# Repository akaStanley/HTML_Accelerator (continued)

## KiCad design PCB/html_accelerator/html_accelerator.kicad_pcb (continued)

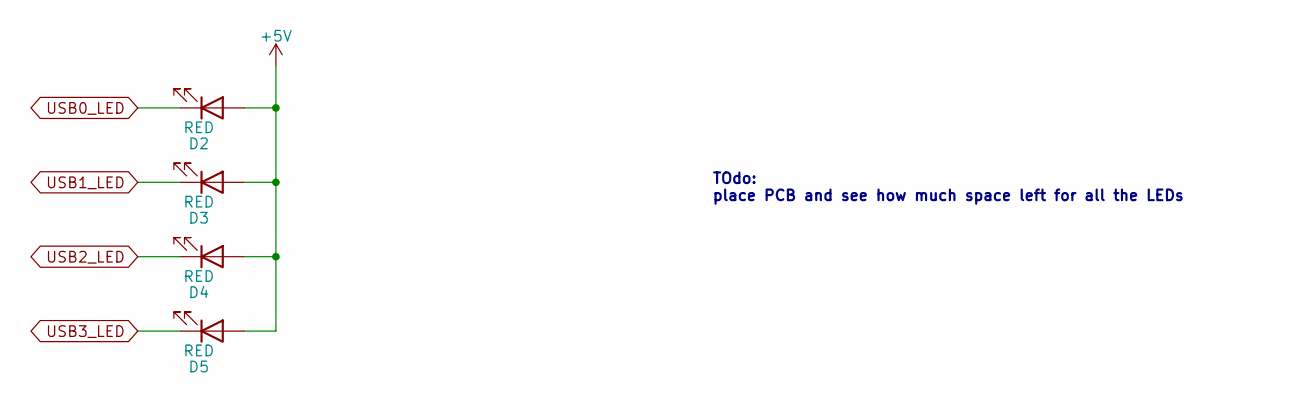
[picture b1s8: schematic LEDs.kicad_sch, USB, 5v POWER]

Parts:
D2, D3, D4, D5: RED; LED_0805_2012Metric_Pad1.15x1.40mm_HandSolder

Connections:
+5V: D2.2 (A), D3.2 (A), D4.2 (A), D5.2 (A); also elsewhere on the board
USB0_LED: D2.1 (K); also elsewhere on the board
USB1_LED: D3.1 (K); also elsewhere on the board
USB2_LED: D4.1 (K); also elsewhere on the board
USB3_LED: D5.1 (K); also elsewhere on the board

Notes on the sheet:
TOdo: place PCB and see how much space left for all the LEDs

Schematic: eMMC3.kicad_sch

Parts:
C52, C53: 4.7uF; C_0805_2012Metric_Pad1.18x1.45mm_HandSolder
C54, C55: 22pF; C_0805_2012Metric_Pad1.18x1.45mm_HandSolder
C56, C57: 2.2uF; C_0805_2012Metric_Pad1.18x1.45mm_HandSolder
C58: 0.1uF; C_0805_2012Metric_Pad1.18x1.45mm_HandSolder
R50: 10k; R_0805_2012Metric_Pad1.20x1.40mm_HandSolder
R51: 1k; R_0805_2012Metric_Pad1.20x1.40mm_HandSolder
R52: 27; R_0805_2012Metric_Pad1.20x1.40mm_HandSolder
R53: 680; R_0805_2012Metric_Pad1.20x1.40mm_HandSolder
U6, U7: EMMC_4G; EMMC04G-M627-X03U_KNT
U9: AU6438BS; SSOP-28_3.9x9.9mm_P0.635mm
Y4: 12MHz; Crystal_SMD_3225-4Pin_3.2x2.5mm

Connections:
90_USB2_D_N: U9.8 (USB_DN); also elsewhere on the board
90_USB2_D_P: U9.7 (USB_DP); also elsewhere on the board
+5V: R50.1, U9.15 (AVDD_5.0_IN); also elsewhere on the board
/eMMC3/DATA_0: U7.A3 (DAT0), U9.27 (DATA0)
/eMMC3/DATA_1: U7.A4 (DAT1), U9.28 (DATA1)
/eMMC3/DATA_2: U7.A5 (DAT2), U9.19 (DATA2)
/eMMC3/DATA_3: U7.B2 (DAT3), U9.20 (DATA3)
/eMMC3/DATA_4: U7.B3 (DAT4), U9.21 (DATA4)
/eMMC3/DATA_5: U7.B4 (DAT5), U9.23 (DATA5)
/eMMC3/DATA_6: U7.B5 (DAT6), U9.25 (DATA6)
/eMMC3/DATA_7: U7.B6 (DAT7), U9.26 (DATA7)
/eMMC3/VDD_3v3_EMMC3: C52.1, C53.1, C56.1, C57.1, U7.C6 (VCCQ), U7.E6 (VCC), U7.F5 (VCC), U7.J10 (VCC), U7.K9 (VCC), U7.M4 (VCCQ), U7.N4 (VCCQ), U7.P3 (VCCQ), U7.P5 (VCCQ), U9.14 (VDD_FLASH_3.3_OUT)
GND: C52.2, C53.2, C54.2, C55.2, C56.2, C57.2, C58.2, R53.2, U7.C4 (VSSQ), U7.E7 (VSS), U7.G5 (VSS), U7.H10 (VSS), U7.K8 (VSS), U7.N2 (VSSQ), U7.N5 (VSSQ), U7.P4 (VSSQ), U7.P6 (VSSQ), U9.1 (SDCDN), U9.2 (SDWP), U9.9 (VSSAREG), U9.12 (VSS), U9.17 (VSSHM), Y4.2, Y4.4; also elsewhere on the board
unnamed: R52.2, U7.M6 (CLK)
unnamed: U7.M5 (CMD), U9.22 (SDCMD)
unnamed: R50.2, U7.K5 (RST_N), U9.4 (#CHIP_RST)
unnamed: C58.1, U7.C2 (VDDI)
unnamed: R53.1, U9.5 (EXT_R)
unnamed: R51.2, U9.3 (LED_ACTIVITY)
unnamed: R52.1, U9.24 (SD_CLK)
unnamed: U9.6 (V3.3_PHY_IN), U9.16 (VDD_3.3_OUT)
unnamed: C54.1, U9.10 (XTAL_IN), Y4.1
unnamed: C55.1, U9.11 (XTAL_OUT), Y4.3
USB2_LED: R51.1; also elsewhere on the board

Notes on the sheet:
4.7uF for VCC/VSS
0.1uF for VDDi/VSSQ
use PNP on LED input
2.2uF for VCCQ/VSSQ

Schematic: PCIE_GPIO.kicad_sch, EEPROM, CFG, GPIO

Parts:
C35: 0.1uF; C_0805_2012Metric_Pad1.18x1.45mm_HandSolder
C36, C37: 22pF; C_0805_2012Metric_Pad1.18x1.45mm_HandSolder
R22, R24, R27: 4.7k; R_0805_2012Metric_Pad1.20x1.40mm_HandSolder
R23: 4.7k; R_0805_2012Metric_Pad1.20x1.40mm_HandSolder; not fitted
R25, R28, R29, R33, R34, R35, R36, R37, R38, R41: 1k; R_0805_2012Metric_Pad1.20x1.40mm_HandSolder
R26, R30, R31, R32, R39, R40: 1k; R_0805_2012Metric_Pad1.20x1.40mm_HandSolder; not fitted
RN1, RN2, RN3, RN4, RN5: 1k; R_Array_Convex_4x1206
U1: MCS9990; LQFP-128_14x14mm_P0.4mm
U3: CAT24C256YI-GT3; TSSOP-8_4.4x3mm_P0.65mm
Y1: 12MHz; Crystal_SMD_HC49-SD

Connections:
3v3_filt: C35.2, R22.1, R23.1, R24.1, R25.1, R26.1, R28.1, U3.8 (VCC); also elsewhere on the board
+3V0: R27.1; also elsewhere on the board
GND: C35.1, C36.2, C37.2, R29.2, R30.2, R31.2, R32.2, R33.2, R34.2, R35.2, R36.2, R37.2, R38.2, R39.2, R40.2, R41.1, RN1.5 (R4.2), RN1.6 (R3.2), RN1.7 (R2.2), RN1.8 (R1.2), RN2.5 (R4.2), RN2.6 (R3.2), RN2.7 (R2.2), RN2.8 (R1.2), RN3.5 (R4.2), RN3.6 (R3.2), RN3.7 (R2.2), RN3.8 (R1.2), RN4.5 (R4.2), RN4.6 (R3.2), RN4.7 (R2.2), RN4.8 (R1.2), RN5.5 (R4.2), RN5.6 (R3.2), RN5.7 (R2.2), RN5.8 (R1.2), U3.4 (GND); also elsewhere on the board
unnamed: RN1.1 (R1.1), U1.35 (GPIO0/D0)
unnamed: RN1.2 (R2.1), U1.36 (GPIO1/D1)
unnamed: RN1.3 (R3.1), U1.37 (GPIO2/D2)
unnamed: RN1.4 (R4.1), U1.38 (GPIO3/D3)
unnamed: RN2.1 (R1.1), U1.39 (GPIO4/D4)
unnamed: RN2.2 (R2.1), U1.40 (GPIO5/D5)
unnamed: RN2.3 (R3.1), U1.41 (GPIO6/D6)
unnamed: RN2.4 (R4.1), U1.42 (GPIO7/D7)
unnamed: RN3.1 (R1.1), U1.43 (GPIO8/INTA)
unnamed: RN3.2 (R2.1), U1.44 (GPIO9/INTB)
unnamed: RN3.3 (R3.1), U1.45 (GPIO10/INTC)
unnamed: RN3.4 (R4.1), U1.46 (GPIO11/INTD)
unnamed: RN4.1 (R1.1), U1.65 (GPIO12/CSA_N)
unnamed: RN4.2 (R2.1), U1.66 (GPIO13/CSB_N)
unnamed: RN4.3 (R3.1), U1.67 (GPIO14/CSC_N)
unnamed: RN4.4 (R4.1), U1.68 (GPIO15/CSD_N)
unnamed: RN5.1 (R1.1), U1.71 (GPIO16/RESET)
unnamed: RN5.2 (R2.1), U1.72 (GPIO17/IOW_N)
unnamed: RN5.3 (R3.1), U1.73 (GPIO18/IOR_N)
unnamed: RN5.4 (R4.1), U1.74 (GPIO23/IOCHRDY2)
unnamed: R38.1, U1.75 (GPIO19/A0)
unnamed: R39.1, U1.76 (GPIO20/A1)
unnamed: R40.1, U1.77 (GPIO21/A2)
unnamed: R41.2, U1.78 (GPIO22/IOCHRDY1)
unnamed: C36.1, U1.81 (USB0_XSCI), Y1.1
unnamed: C37.1, U1.82 (USB0_XSCO), Y1.2
unnamed: R25.2, U1.29 (EE_SCL), U3.6 (SCL)
unnamed: R28.2, U1.30 (EE_SDA), U3.5 (SDA)
unnamed: R29.1, U1.60 (JTAG_TCK)
unnamed: R24.2, U1.104 (LN_STAT0)
unnamed: R23.2, U1.105 (LN_STAT1)
unnamed: R27.2, U1.101 (LN_STAT2)
unnamed: R33.1, U1.24 (MODE_SEL0)
unnamed: R34.1, U1.47 (MODE_SEL1)
unnamed: R35.1, U1.49 (MODE_SEL2)
unnamed: R22.2, U1.27 (OTG_EN_N)
unnamed: R36.1, U1.31 (SCAN_EN)
unnamed: R37.1, U1.32 (TEST_EN)
unnamed: R30.1, U3.1 (A0)
unnamed: R31.1, U3.2 (A1)
unnamed: R32.1, U3.3 (A2)
unnamed: R26.2, U3.7 (WP)

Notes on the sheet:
A0,A1,A2 Boostrap Options
(GPIOs disabled in 4 USB HOST mode)
Write Protect Lock EEPROM when HIGH
Addr A0,A1,A2 internal PD

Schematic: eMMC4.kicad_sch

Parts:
C59, C60: 4.7uF; C_0805_2012Metric_Pad1.18x1.45mm_HandSolder
C61, C62: 22pF; C_0805_2012Metric_Pad1.18x1.45mm_HandSolder
C63, C64: 2.2uF; C_0805_2012Metric_Pad1.18x1.45mm_HandSolder
C65: 0.1uF; C_0805_2012Metric_Pad1.18x1.45mm_HandSolder
R54: 10k; R_0805_2012Metric_Pad1.20x1.40mm_HandSolder
R55: 1k; R_0805_2012Metric_Pad1.20x1.40mm_HandSolder
R56: 27; R_0805_2012Metric_Pad1.20x1.40mm_HandSolder
R57: 680; R_0805_2012Metric_Pad1.20x1.40mm_HandSolder
U10: AU6438BS; SSOP-28_3.9x9.9mm_P0.635mm
U11: EMMC_4G; EMMC04G-M627-X03U_KNT
Y5: 12MHz; Crystal_SMD_3225-4Pin_3.2x2.5mm

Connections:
90_USB3_D_N: U10.8 (USB_DN); also elsewhere on the board
90_USB3_D_P: U10.7 (USB_DP); also elsewhere on the board
+5V: R54.1, U10.15 (AVDD_5.0_IN); also elsewhere on the board
/eMMC4/DATA_0: U10.27 (DATA0), U11.A3 (DAT0)
/eMMC4/DATA_1: U10.28 (DATA1), U11.A4 (DAT1)
/eMMC4/DATA_2: U10.19 (DATA2), U11.A5 (DAT2)
/eMMC4/DATA_3: U10.20 (DATA3), U11.B2 (DAT3)
/eMMC4/DATA_4: U10.21 (DATA4), U11.B3 (DAT4)
/eMMC4/DATA_5: U10.23 (DATA5), U11.B4 (DAT5)
/eMMC4/DATA_6: U10.25 (DATA6), U11.B5 (DAT6)
/eMMC4/DATA_7: U10.26 (DATA7), U11.B6 (DAT7)
/eMMC4/VDD_3v3_EMMC4: C59.1, C60.1, C63.1, C64.1, U10.14 (VDD_FLASH_3.3_OUT), U11.C6 (VCCQ), U11.E6 (VCC), U11.F5 (VCC), U11.J10 (VCC), U11.K9 (VCC), U11.M4 (VCCQ), U11.N4 (VCCQ), U11.P3 (VCCQ), U11.P5 (VCCQ)
GND: C59.2, C60.2, C61.2, C62.2, C63.2, C64.2, C65.2, R57.2, U10.1 (SDCDN), U10.2 (SDWP), U10.9 (VSSAREG), U10.12 (VSS), U10.17 (VSSHM), U11.C4 (VSSQ), U11.E7 (VSS), U11.G5 (VSS), U11.H10 (VSS), U11.K8 (VSS), U11.N2 (VSSQ), U11.N5 (VSSQ), U11.P4 (VSSQ), U11.P6 (VSSQ), Y5.2, Y5.4; also elsewhere on the board
unnamed: R54.2, U10.4 (#CHIP_RST), U11.K5 (RST_N)
unnamed: R57.1, U10.5 (EXT_R)
unnamed: R55.2, U10.3 (LED_ACTIVITY)
unnamed: U10.22 (SDCMD), U11.M5 (CMD)
unnamed: R56.1, U10.24 (SD_CLK)
unnamed: U10.6 (V3.3_PHY_IN), U10.16 (VDD_3.3_OUT)
unnamed: C61.1, U10.10 (XTAL_IN), Y5.1
unnamed: C62.1, U10.11 (XTAL_OUT), Y5.3
unnamed: R56.2, U11.M6 (CLK)
unnamed: C65.1, U11.C2 (VDDI)
USB3_LED: R55.1; also elsewhere on the board

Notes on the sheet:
4.7uF for VCC/VSS
0.1uF for VDDi/VSSQ
use PNP on LED input
2.2uF for VCCQ/VSSQ

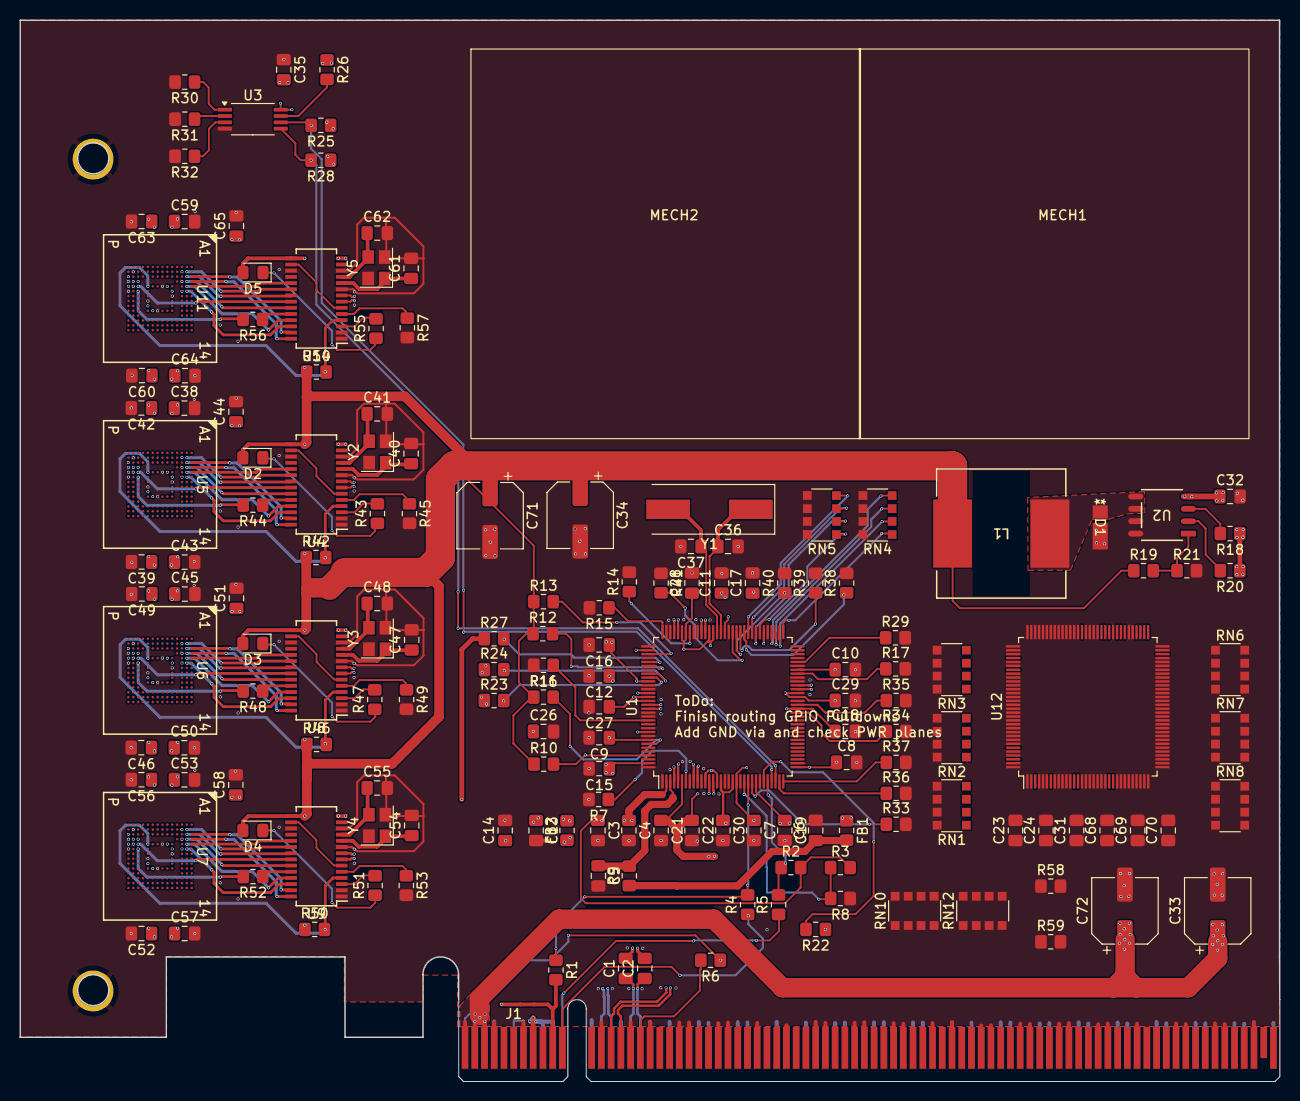
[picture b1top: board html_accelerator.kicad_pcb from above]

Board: 4 copper layers, 129.3 x 109.0 mm, 166 parts (0 on the bottom side), 168 nets.

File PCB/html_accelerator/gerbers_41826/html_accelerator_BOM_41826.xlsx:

Comment | Designator | Footprint | JLCPCB Part #（optional）
0.1uF | C1,C2,C4,C6,C8,C9,C10,C11,C12,C13,C15,C16,C17,C18,C19,C22,C23,C24,C27,C28,C29,C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 | Capacitor_SMD:C_0805_2012Metric_Pad1.18x1.45mm_HandSolder
10uF | C3,C7,C14,C21,C26 | Capacitor_SMD:C_0805_2012Metric_Pad1.18x1.45mm_HandSolder
3.3uF | C5 | Capacitor_SMD:C_0805_2012Metric_Pad1.18x1.45mm_HandSolder
100uF | C33,C34,C71,C72 | Capacitor_SMD:CP_Elec_6.3x5.8
22pF | C36,C37,C40,C41,C47,C48,C54,C55,C61,C62 | Capacitor_SMD:C_0805_2012Metric_Pad1.18x1.45mm_HandSolder
4.7uF | C38,C39,C45,C46,C52,C53,C59,C60 | Capacitor_SMD:C_0805_2012Metric_Pad1.18x1.45mm_HandSolder
2.2uF | C42,C43,C49,C50,C56,C57,C63,C64 | Capacitor_SMD:C_0805_2012Metric_Pad1.18x1.45mm_HandSolder
SBR2U30P1 | D1 | html_accel_footprints:DIODE_SBR3M30P1_1P78X2P8_DIO-M
RED | D2,D3,D4,D5 | LED_SMD:LED_0805_2012Metric_Pad1.15x1.40mm_HandSolder
BLM21PG121SN1D | FB1,FB2 | Resistor_SMD:R_0805_2012Metric_Pad1.20x1.40mm_HandSolder
NOSTUFF | HEATSINK1,HEATSINK2 | html_accel_footprints:Heatsink
NOSTUFF | J1 | Connector_PCBEdge:BUS_PCIexpress_x16
NOSTUFF | J2 | html_accel_footprints:PCIexpress_bracket_full
SRR1208-330YL | L1 | html_accel_footprints:IND_BOURNS_SRR1208
NOSTUFF | R1,R2,R3,R23 | Resistor_SMD:R_0805_2012Metric_Pad1.20x1.40mm_HandSolder
33 | R4 | Resistor_SMD:R_0805_2012Metric_Pad1.20x1.40mm_HandSolder
0 | R5,R6,R9,R58,R59,R60,R61,R62,R63 | Resistor_SMD:R_0805_2012Metric_Pad1.20x1.40mm_HandSolder
6.2k | R7 | Resistor_SMD:R_0805_2012Metric_Pad1.20x1.40mm_HandSolder
NOSTUFF | R8,R26,R30,R31,R32,R39,R40 | Resistor_SMD:R_0805_2012Metric_Pad1.20x1.40mm_HandSolder
10k | R10,R11,R12,R13,R42,R46,R50,R54 | Resistor_SMD:R_0805_2012Metric_Pad1.20x1.40mm_HandSolder
12k | R14,R15,R16,R17 | Resistor_SMD:R_0805_2012Metric_Pad1.20x1.40mm_HandSolder
3k | R18 | Resistor_SMD:R_0805_2012Metric_Pad1.20x1.40mm_HandSolder
6.8k | R19 | Resistor_SMD:R_0805_2012Metric_Pad1.20x1.40mm_HandSolder
1k | R20,R25,R28,R29,R33,R34,R35,R36,R37,R38,R41,R43,R47,R51,R55 | Resistor_SMD:R_0805_2012Metric_Pad1.20x1.40mm_HandSolder
1.3k | R21 | Resistor_SMD:R_0805_2012Metric_Pad1.20x1.40mm_HandSolder
4.7k | R22,R24,R27 | Resistor_SMD:R_0805_2012Metric_Pad1.20x1.40mm_HandSolder
27 | R44,R48,R52,R56 | Resistor_SMD:R_0805_2012Metric_Pad1.20x1.40mm_HandSolder
680 | R45,R49,R53,R57 | Resistor_SMD:R_0805_2012Metric_Pad1.20x1.40mm_HandSolder
1k | RN1,RN2,RN3,RN4,RN5,RN6,RN7,RN8,RN10,RN12 | Resistor_SMD:R_Array_Convex_4x1206
MCS9990 | U1,U12 | Package_QFP:LQFP-128_14x14mm_P0.4mm
AP1513 | U2 | html_accel_footprints:SOP-8L_DIO
CAT24C256YI-GT3 | U3 | Package_SO:TSSOP-8_4.4x3mm_P0.65mm
AU6438BS | U4,U8,U9,U10 | Package_SO:SSOP-28_3.9x9.9mm_P0.635mm
EMMC_4G | U5,U6,U7,U11 | html_accel_footprints:EMMC04G-M627-X03U_KNT
12MHz | Y1 | Crystal:Crystal_SMD_HC49-SD
12MHz | Y2,Y3,Y4,Y5 | Crystal:Crystal_SMD_3225-4Pin_3.2x2.5mm

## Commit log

2023-05-05 Architecture docs and datasheets
    Architecture docs and info, some datasheets
2023-05-05 Markdown formatting
2023-05-07 Create KiCAD Project
    Import Schematic symbols and footprints
2023-05-09 Creation of VT6212 schematic symbol PCIE, TEST, EEPROM, NC
2023-05-10 Add USB and POWER schematic blocks for VT6212
2023-05-11 Sch Symbol updates and cleanup
2023-05-11 update symbols and create sch pages
2024-09-03 Update to MCS9990 for PCIE direct to USB
2024-09-03 Update todo list
2024-09-03 Schematic edits
2024-09-14 PCIE connections wired
2024-09-15 block diagram, datasheet updates
2024-09-16 schematic updates
2024-09-17 Voltage regulator and footprints
2024-09-22 EMMC symbol and footprint update
2024-09-23 EMMC symbols and netlist
2024-09-23 provision for LEDs
2024-09-30 3d part models, PCB netlist imported
2024-09-30 3D model updates
2024-09-30 cap updates
2024-10-07 placement updates
2024-10-07 layout and 3d updates
2024-10-07 impedance controlled nets
2024-10-07 before update Kicad version
2024-10-08 constraints for impedance control
2024-10-08 PCIE routing+Shield
2024-10-08 trace routing
2024-11-17 Impedance control routing 90 and 85 ohm
2024-11-17 todolist for routing
2024-11-18 highspeed routing + EMMC routing #1
2024-11-18 EMMC wiring checkpoint
2024-11-18 routing checkpoint
2024-11-18 nearly done routing
2026-04-06 Ongoing layout, Update to Kicad V10
2026-04-06 Trace cleanup
2026-04-06 DRC cleanup in progress
2026-04-06 Clean DRC, ready for GND via add
2026-04-19 Additional routing greebles, cleanup and gerber export with BOM
2026-04-26 85ohm trace routing update, pending 90ohm
2026-04-26 impedance control net tuning and gnd shield via stitch
2026-04-26 gerbers and readme updates
2026-04-26 readme updates
2026-04-29 footprint updates for EMMC
2026-04-30 updated gerbers for fab
2026-06-20 update D1 footprint to correct bad symbol pin 1, new gerbers generated
2026-06-23 more storytelling updates
2026-06-28 More story and images
2026-06-28 story and images
2026-06-28 formatting
2026-06-28 jpeg shenanigans
2026-06-28 readme
2026-06-28 first draft story
2026-06-28 proofreading (I did not sleep)
2026-06-28 story updates
2026-06-29 Story with final pictures
2026-06-29 File cleanup
2026-06-29 Updated photo
